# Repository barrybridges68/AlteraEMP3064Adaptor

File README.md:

# AlteraEMP3064Adaptor
Altera EMP3064 Adaptor for 44 TQFP

Simple adapotor board with 3v3 reg

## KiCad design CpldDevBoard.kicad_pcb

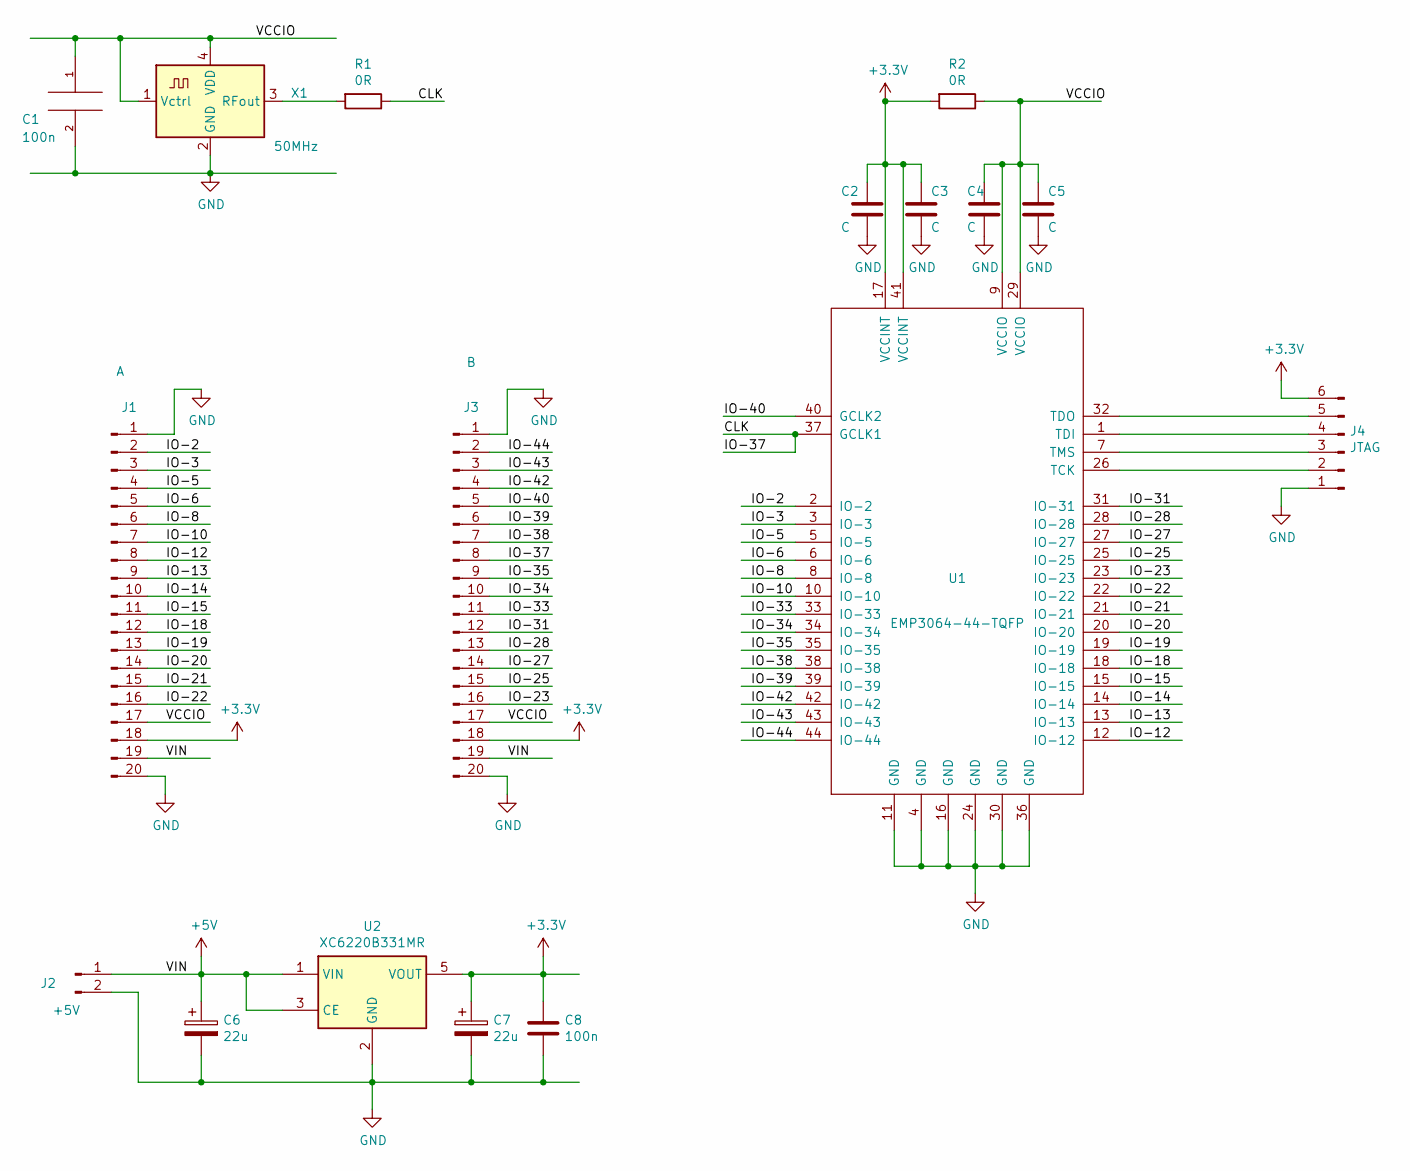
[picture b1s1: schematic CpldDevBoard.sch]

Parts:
C1, C8: 100n; C_0603_HandSoldering
C2, C3, C4, C5: C; C_0603_HandSoldering
C6, C7: 22u; CP_Tantalum_Case-A_EIA-3216-18_Reflow
J1: A; Pin_Header_Straight_1x20_Pitch2.54mm
J2: +5V; Pin_Header_Straight_1x02_Pitch2.54mm
J3: B; Pin_Header_Straight_1x20_Pitch2.54mm
J4: JTAG; Pin_Header_Straight_1x06_Pitch2.54mm
R1, R2: 0R; R_0603_HandSoldering
U1: EMP3064-44-TQFP; LQFP-44_10x10mm_Pitch0.8mm
U2: XC6220B331MR; SOT-23-5
X1: 50MHz; Oscillator_SMD_EuroQuartz_XO32-4pin_3.2x2.5mm_HandSoldering

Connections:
+3V3: C2.1, C3.1, C7.1, C8.1, J1.18, J3.18, J4.6, R2.2, U1.17 (VCCINT), U1.41 (VCCINT), U2.5 (VOUT)
+5V: C6.1, J1.19, J2.1, J3.19, U2.1 (VIN), U2.3 (CE)
/CLK: J3.8, R1.1, U1.37 (GCLK1)
/IO-2: J1.2, U1.2 (IO-2)
/IO-3: J1.3, U1.3 (IO-3)
/IO-5: J1.4, U1.5 (IO-5)
/IO-6: J1.5, U1.6 (IO-6)
/IO-8: J1.6, U1.8 (IO-8)
/IO-10: J1.7, U1.10 (IO-10)
/IO-12: J1.8, U1.12 (IO-12)
/IO-13: J1.9, U1.13 (IO-13)
/IO-14: J1.10, U1.14 (IO-14)
/IO-15: J1.11, U1.15 (IO-15)
/IO-18: J1.12, U1.18 (IO-18)
/IO-19: J1.13, U1.19 (IO-19)
/IO-20: J1.14, U1.20 (IO-20)
/IO-21: J1.15, U1.21 (IO-21)
/IO-22: J1.16, U1.22 (IO-22)
/IO-23: J3.16, U1.23 (IO-23)
/IO-25: J3.15, U1.25 (IO-25)
/IO-27: J3.14, U1.27 (IO-27)
/IO-28: J3.13, U1.28 (IO-28)
/IO-31: J3.12, U1.31 (IO-31)
/IO-33: J3.11, U1.33 (IO-33)
/IO-34: J3.10, U1.34 (IO-34)
/IO-35: J3.9, U1.35 (IO-35)
/IO-38: J3.7, U1.38 (IO-38)
/IO-39: J3.6, U1.39 (IO-39)
/IO-40: J3.5, U1.40 (GCLK2)
/IO-42: J3.4, U1.42 (IO-42)
/IO-43: J3.3, U1.43 (IO-43)
/IO-44: J3.2, U1.44 (IO-44)
/VCCIO: C1.1, C4.1, C5.1, J1.17, J3.17, R2.1, U1.9 (VCCIO), U1.29 (VCCIO), X1.1 (Vctrl), X1.4 (VDD)
GND: C1.2, C2.2, C3.2, C4.2, C5.2, C6.2, C7.2, C8.2, J1.1, J1.20, J2.2, J3.1, J3.20, J4.1, U1.4 (GND), U1.11 (GND), U1.16 (GND), U1.24 (GND), U1.30 (GND), U1.36 (GND), U2.2 (GND), X1.2 (GND)
unnamed: J4.2, U1.26 (TCK)
unnamed: J4.3, U1.7 (TMS)
unnamed: J4.4, U1.1 (TDI)
unnamed: J4.5, U1.32 (TDO)
unnamed: R1.2, X1.3 (RFout)

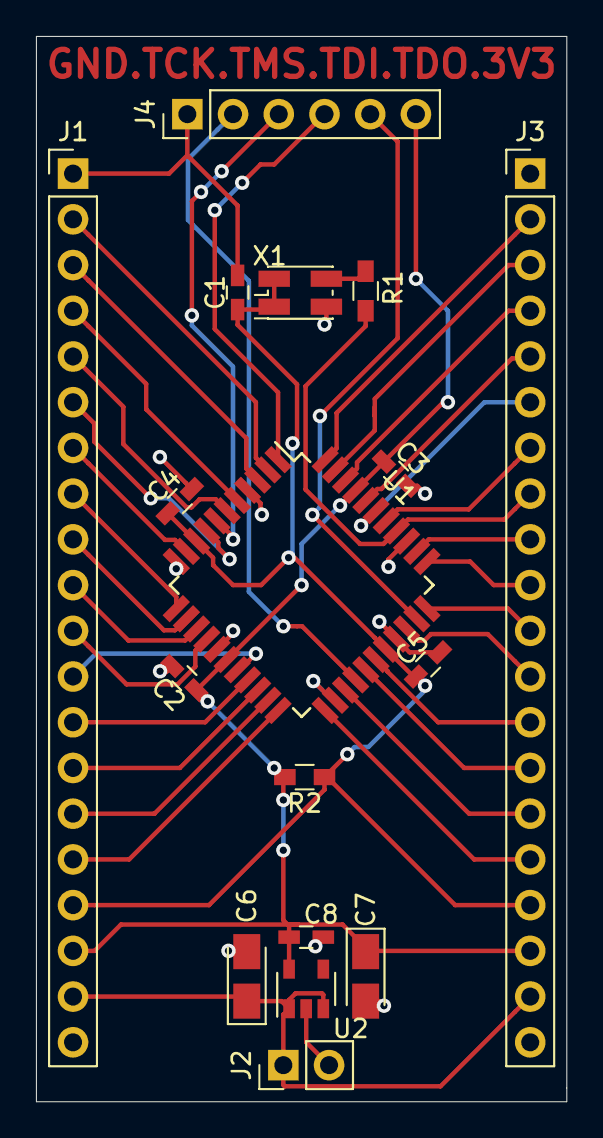
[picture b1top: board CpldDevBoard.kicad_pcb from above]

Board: 2 copper layers, 29.5 x 59.2 mm, 17 parts (0 on the bottom side), 39 nets.
